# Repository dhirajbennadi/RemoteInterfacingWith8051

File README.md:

# Remote Interfacing with 8051

The project aims to allow the user to flash and test their binaries on the flash memory of 8051.\
This is achieved by connecting the 8051 to a target microcontroller, MSP432P401R in this case and connect the user to the target controller via a Wi-Fi module, ESP32.\
The project also aims to design a PCB for the target system consisting of the MSP432 controller, ESP32 module, LCD module and the 8051 microcontroller.\
The project extends in providing the user with a utility to connect to network and to allow selection of hex files.

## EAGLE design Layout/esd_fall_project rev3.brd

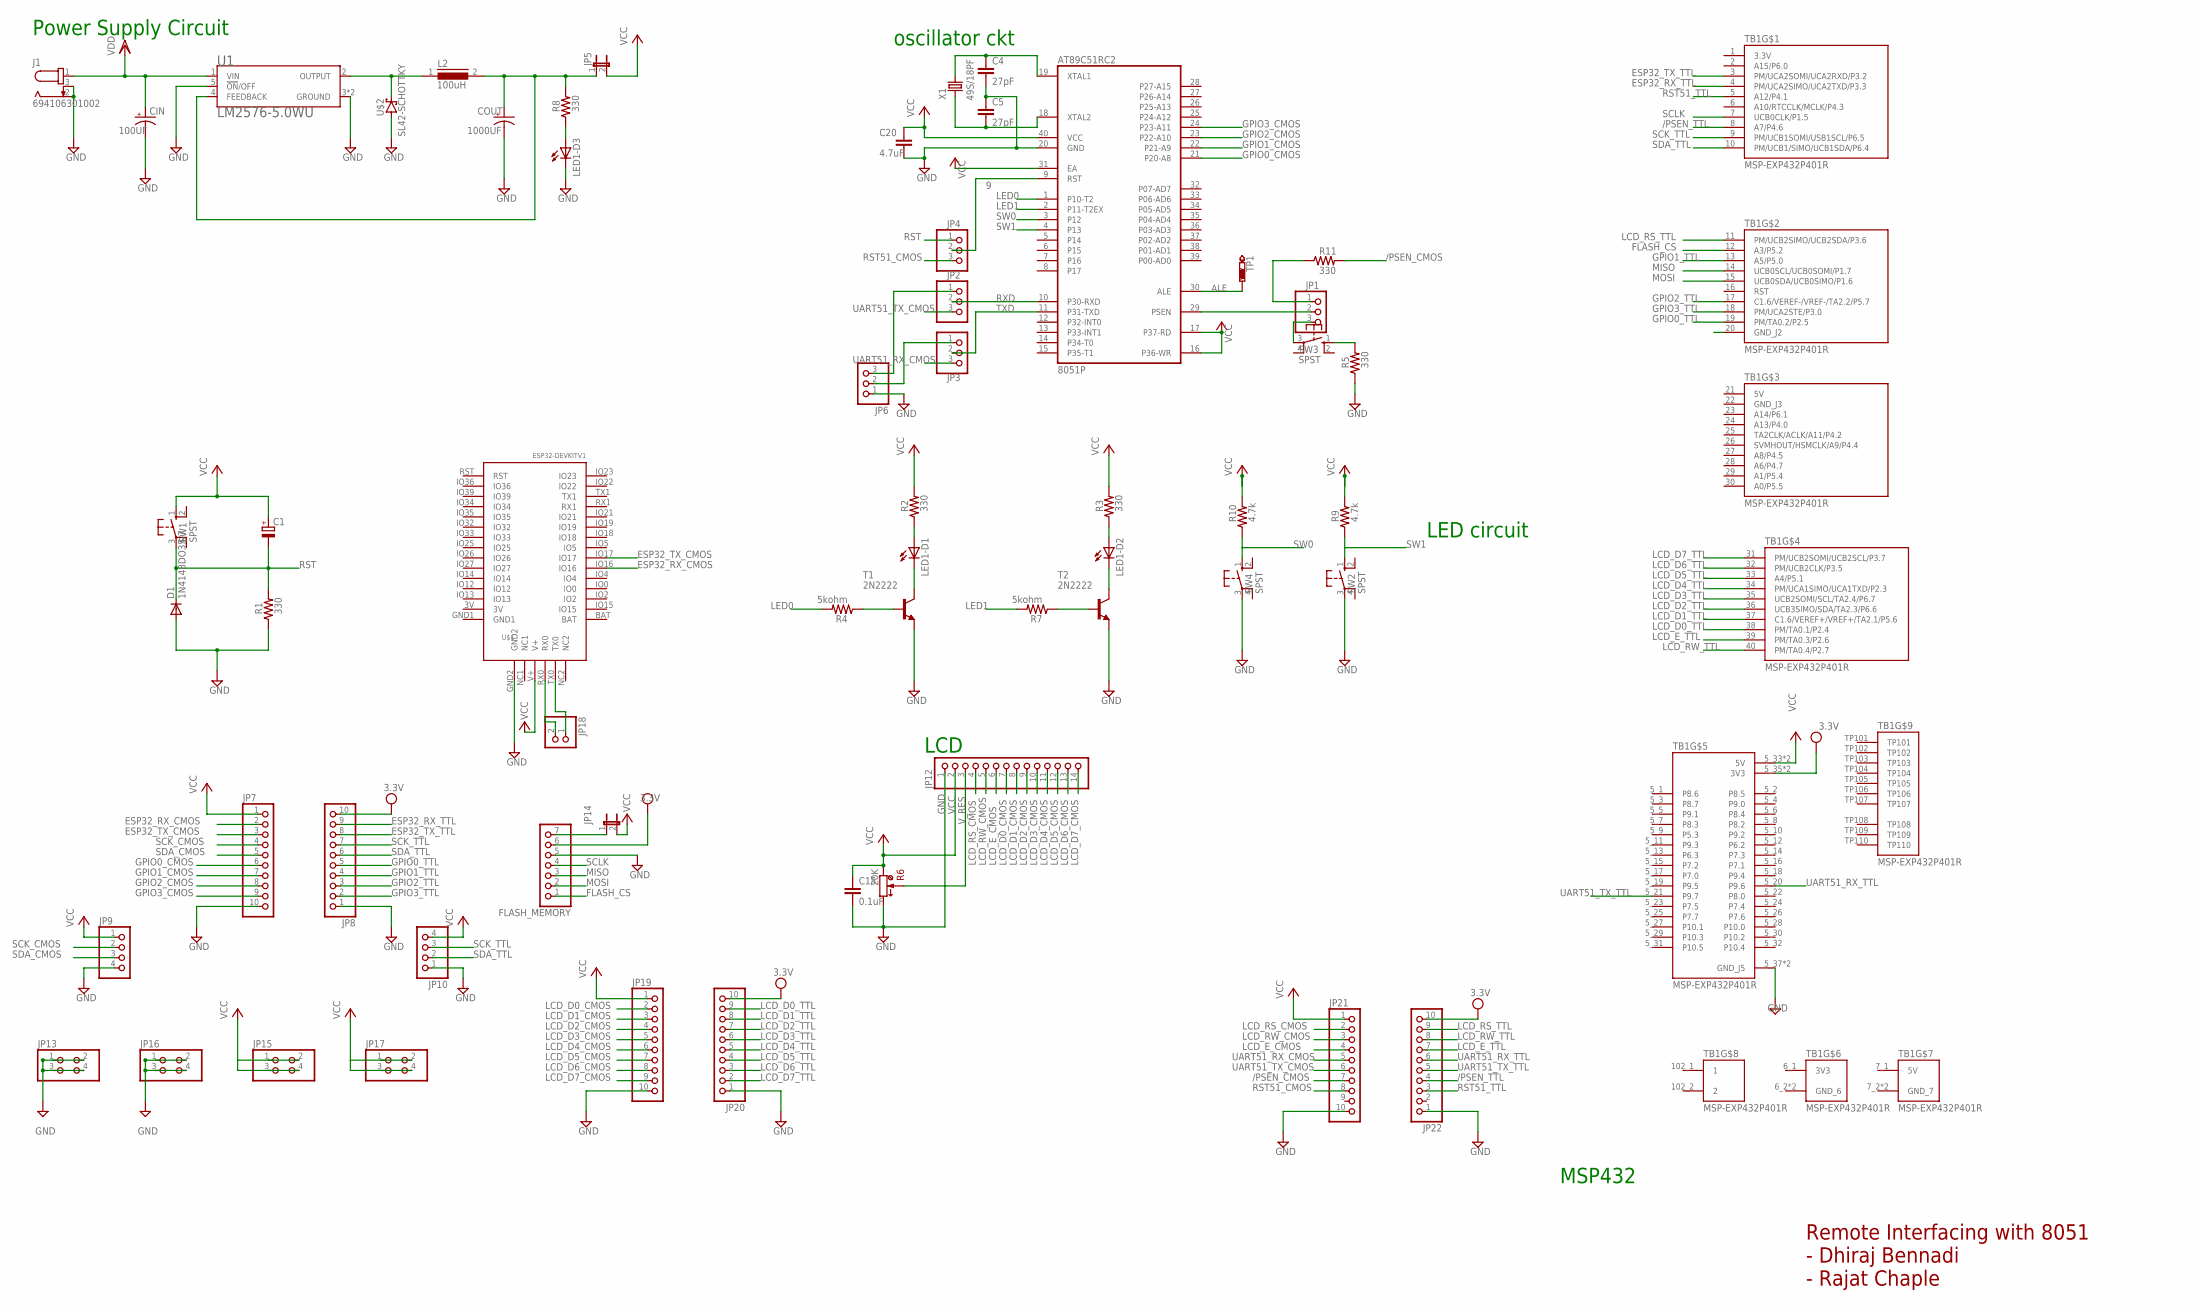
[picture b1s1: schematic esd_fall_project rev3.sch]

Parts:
AT89C51RC2: 8051P; DIL40
C1: CPOL-EUE1.8-4; E1,8-4
C4, C5: 27pF; C2.5-3
C15: 0.1uF; C2.5-3
C20: 4.7uF; C2.5-3
CIN: 100UF; 153CLV-1014
COUT: 1000UF; 150CLZ-1010
D1: 1N4148DO35-7; DO35-7
FLASH_MEMORY: PINHD-1X7; 1X07
J1: 694106301002
JP1, JP2, JP3, JP4, JP6: PINHD-1X3; 1X03
JP5, JP14: JP1E; JP1
JP7, JP8, JP19, JP20, JP21, JP22: PINHD-1X10; 1X10
JP9, JP10: PINHD-1X4; 1X04
JP12: PINHD-1X14; 1X14
JP13, JP15, JP16, JP17: PINHD-2X2; 2X02
JP18: PINHD-1X2; 1X02
L2: 100uH; DR127
LED1-D1, LED1-D2, LED1-D3: LED5MM
R1, R2, R3, R5, R8, R11: 330; 0204/7
R4, R7: 5kohm; 0204/7
R6: 20K; 64W
R9, R10: 4.7k; 0204/7
SW1, SW2, SW3, SW4: SPST; B3F-10XX; MPN B3F-1000
T1, T2: 2N2222; TO18
TB1: MSP-EXP432P401R; SHIELD_MSP-EXP432P401R
TP1: PTR1B2,54; B2,54
U1: LM2576-5.0WU; DPAK6P170_1524X459L254X81N
U$1: ESP32DEVKITV1; ESP32-DEVKITV1
U$2: SL42-SCHOTTKY; SMC
X1: 49S/18PF; XTAL_HC49

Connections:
3.3V: JP8.10, JP20.10, JP22.10
3V3: TB1.6_1 (3V3)
5V: TB1.7_1 (5V), TB1.21 (5V)
9: AT89C51RC2.9 (RST), JP4.2
/PSEN_CMOS: JP21.7, R11.2
/PSEN_TTL: JP22.4, TB1.8 (A7/P4.6)
ALE: AT89C51RC2.30 (ALE), TP1.TP
ESP32_RX_CMOS: JP7.2, U$1.IO16
ESP32_RX_TTL: JP8.9, TB1.4 (PM/UCA2SIMO/UCA2TXD/P3.3)
ESP32_TX_CMOS: JP7.3, U$1.IO17
ESP32_TX_TTL: JP8.8, TB1.3 (PM/UCA2SOMI/UCA2RXD/P3.2)
FLASH_CS: FLASH_MEMORY.1, TB1.12 (A3/P5.2)
GND: AT89C51RC2.20 (GND), C4.2, C5.1, C15.2, C20.2, CIN.-, COUT.-, D1.A, FLASH_MEMORY.5, J1.2, J1.3, JP6.1, JP7.10, JP8.1, JP9.4, JP10.1, JP12.1, JP13.1, JP13.2, JP13.3, JP13.4, JP16.1, JP16.2, JP16.3, JP16.4, JP19.10, JP20.1, JP21.10, JP22.1, LED1-D3.K (C), R1.1, R5.1, R6.3 (CW), SW2.3, SW4.3, T1.1 (E), T2.1 (E), TB1.5_37 (GND_J5), TB1.5_38 (GND_J5), U1.3 (GROUND), U1.5 (!ON!/OFF), U1.6 (GROUND), U$1.GND2, U$2.A
GND_6: TB1.6_2 (GND_6), TB1.6_3 (GND_6)
GND_7: TB1.7_2 (GND_7), TB1.7_3 (GND_7)
GND_J3: TB1.22 (GND_J3)
GPIO0_CMOS: AT89C51RC2.21 (P20-A8), JP7.6
GPIO0_TTL: JP8.5, TB1.19 (PM/TA0.2/P2.5)
GPIO1_CMOS: AT89C51RC2.22 (P21-A9), JP7.7
GPIO1_TTL: JP8.4, TB1.13 (A5/P5.0)
GPIO2_CMOS: AT89C51RC2.23 (P22-A10), JP7.8
GPIO2_TTL: JP8.3, TB1.17 (C1.6/VEREF-/VREF-/TA2.2/P5.7)
GPIO3_CMOS: AT89C51RC2.24 (P23-A11), JP7.9
GPIO3_TTL: JP8.2, TB1.18 (PM/UCA2STE/P3.0)
LCD_D0_CMOS: JP12.7, JP19.2
LCD_D0_TTL: JP20.9, TB1.38 (PM/TA0.1/P2.4)
LCD_D1_CMOS: JP12.8, JP19.3
LCD_D1_TTL: JP20.8, TB1.37 (C1.6/VEREF+/VREF+/TA2.1/P5.6)
LCD_D2_CMOS: JP12.9, JP19.4
LCD_D2_TTL: JP20.7, TB1.36 (UCB3SIMO/SDA/TA2.3/P6.6)
LCD_D3_CMOS: JP12.10, JP19.5
LCD_D3_TTL: JP20.6, TB1.35 (UCB2SOMI/SCL/TA2.4/P6.7)
LCD_D4_CMOS: JP12.11, JP19.6
LCD_D4_TTL: JP20.5, TB1.34 (PM/UCA1SIMO/UCA1TXD/P2.3)
LCD_D5_CMOS: JP12.12, JP19.7
LCD_D5_TTL: JP20.4, TB1.33 (A4/P5.1)
LCD_D6_CMOS: JP12.13, JP19.8
LCD_D6_TTL: JP20.3, TB1.32 (PM/UCB2CLK/P3.5)
LCD_D7_CMOS: JP12.14, JP19.9
LCD_D7_TTL: JP20.2, TB1.31 (PM/UCB2SOMI/UCB2SCL/P3.7)
LCD_E_CMOS: JP12.6, JP21.4
LCD_E_TTL: JP22.7, TB1.39 (PM/TA0.3/P2.6)
LCD_RS_CMOS: JP12.4, JP21.2
LCD_RS_TTL: JP22.9, TB1.11 (PM/UCB2SIMO/UCB2SDA/P3.6)
LCD_RW_CMOS: JP12.5, JP21.3
LCD_RW_TTL: JP22.8, TB1.40 (PM/TA0.4/P2.7)
LED0: AT89C51RC2.1 (P10-T2), R4.2
LED1: AT89C51RC2.2 (P11-T2EX), R7.2
MISO: FLASH_MEMORY.3, TB1.14 (UCB0SCL/UCB0SOMI/P1.7)
MOSI: FLASH_MEMORY.2, TB1.15 (UCB0SDA/UCB0SIMO/P1.6)
unnamed: R7.1, T2.2 (B)
unnamed: LED1-D2.A, R3.1
unnamed: COUT.+, JP5.1, L2.2, R8.2, U1.4 (FEEDBACK)
unnamed: L2.1, U1.2 (OUTPUT), U$2.C
unnamed: JP2.1, JP6.3
unnamed: JP3.1, JP6.2
unnamed: R4.1, T1.2 (B)
unnamed: AT89C51RC2.19 (XTAL1), C4.1, X1.2
unnamed: AT89C51RC2.18 (XTAL2), C5.2, X1.1
unnamed: LED1-D1.A, R2.1
unnamed: LED1-D3.A, R8.1
unnamed: AT89C51RC2.29 (PSEN), JP1.2
unnamed: JP18.2, U$1.RX0
unnamed: LED1-D1.K (C), T1.3 (C)
unnamed: JP18.1, U$1.TX0
unnamed: LED1-D2.K (C), T2.3 (C)
unnamed: FLASH_MEMORY.7, JP14.1
unnamed: R5.2, SW3.1 (S)
unnamed: JP1.3, SW3.3
unnamed: JP1.1, R11.1
RST: C1.-, D1.C, JP4.1, R1.2, SW1.3
RST51_CMOS: JP4.3, JP21.8
RST51_TTL: JP22.3, TB1.5 (A12/P4.1)
RXD: AT89C51RC2.10 (P30-RXD), JP2.2
SCK_CMOS: JP7.4, JP9.2
SCK_TTL: JP8.7, JP10.3, TB1.9 (PM/UCB1SOMI/USB1SCL/P6.5)
SCLK: FLASH_MEMORY.4, TB1.7 (UCB0CLK/P1.5)
SDA_CMOS: JP7.5, JP9.3
SDA_TTL: JP8.6, JP10.2, TB1.10 (PM/UCB1/SIMO/UCB1SDA/P6.4)
SW0: AT89C51RC2.3 (P12), R10.1, SW4.1 (S)
SW1: AT89C51RC2.4 (P13), R9.1, SW2.1 (S)
TXD: AT89C51RC2.11 (P31-TXD), JP3.2
UART51_RX_CMOS: JP3.3, JP21.5
UART51_RX_TTL: JP22.6, TB1.5_20 (P9.6)
UART51_TX_CMOS: JP2.3, JP21.6
UART51_TX_TTL: JP22.5, TB1.5_21 (P9.7)
VCC: AT89C51RC2.16 (P36-WR), AT89C51RC2.17 (P37-RD), AT89C51RC2.31 (EA), AT89C51RC2.40 (VCC), C1.+, C15.1, C20.1, JP5.2, JP7.1, JP9.1, JP10.4, JP12.2, JP14.2, JP15.1, JP15.2, JP15.3, JP15.4, JP17.1, JP17.2, JP17.3, JP17.4, JP19.1, JP21.1, R2.2, R3.2, R6.1 (CCW), R9.2, R10.2, SW1.1 (S), TB1.5_33 (5V), TB1.5_34 (5V), U$1.V+
VDD: CIN.+, FLASH_MEMORY.6, J1.1, TB1.5_35 (3V3), TB1.5_36 (3V3), U1.1 (VIN)
V_RES: JP12.3, R6.S (W), R6.S@1 (W)

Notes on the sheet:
Power Supply Circuit
oscillator ckt
LED circuit
LCD
MSP432
Remote Interfacing with 8051 - Dhiraj Bennadi - Rajat Chaple

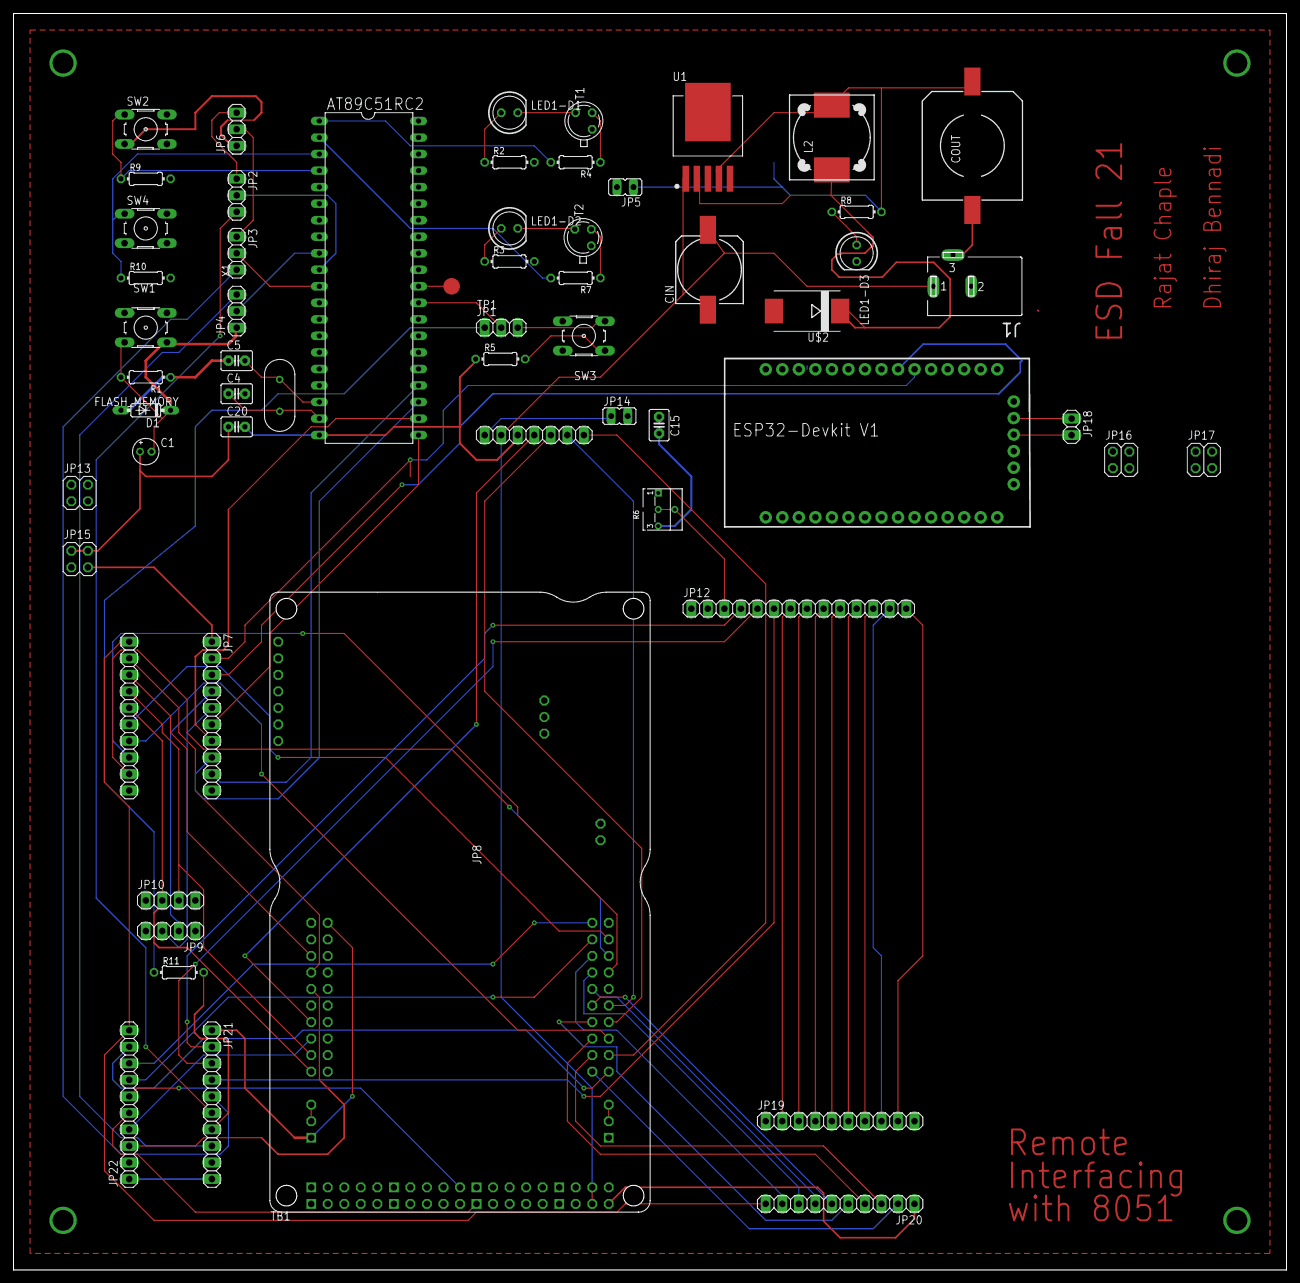
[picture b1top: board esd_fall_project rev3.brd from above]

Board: 2 copper layers, 195.6 x 193.0 mm, 59 parts (0 on the bottom side), 87 nets.

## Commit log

2022-02-01 Code and Documents
